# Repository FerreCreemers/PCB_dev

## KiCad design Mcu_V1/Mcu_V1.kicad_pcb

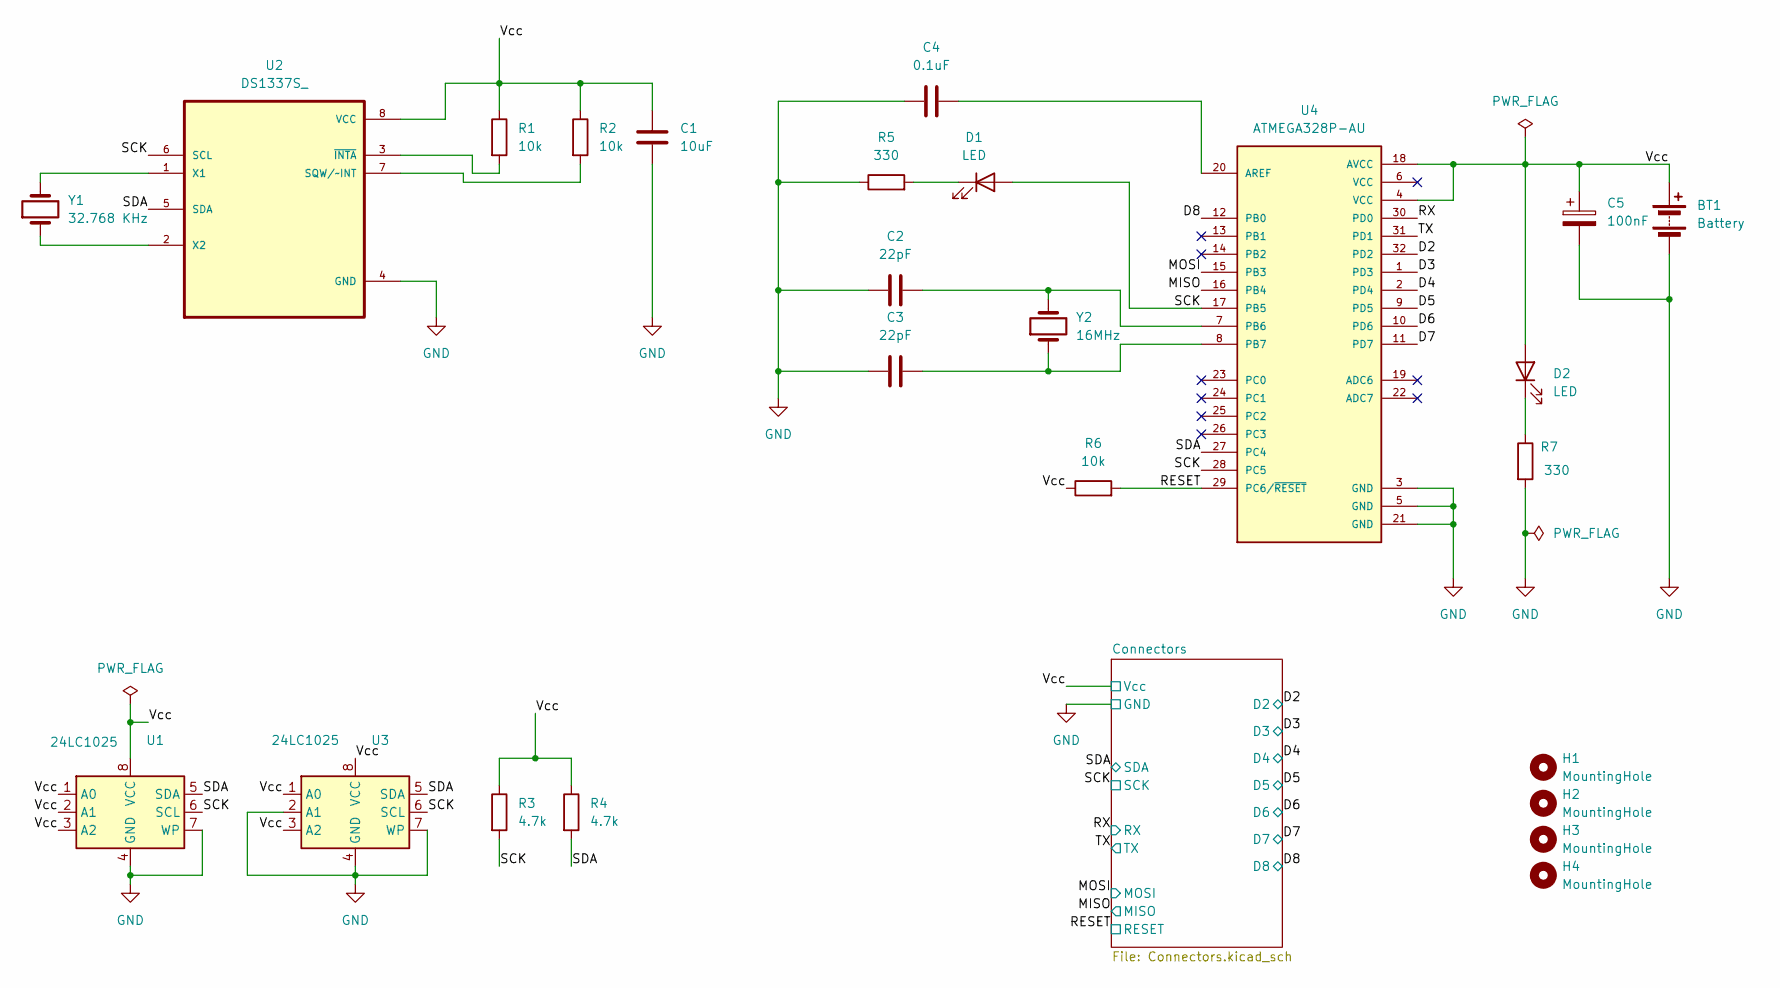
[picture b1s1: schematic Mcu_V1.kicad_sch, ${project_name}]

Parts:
BT1: Battery; PinHeader_1x02_P2.54mm_Vertical
C1: 10uF; C_0805_2012Metric
C2, C3: 22pF; C_0805_2012Metric
C4: 0.1uF; C_0805_2012Metric
C5: 100nF; C_0805_2012Metric
D1, D2: LED; LED_0805_2012Metric
H1, H2, H3, H4: MountingHole; MountingHole_2.1mm
R1, R2, R6: 10k; R_0805_2012Metric
R3, R4: 4.7k; R_0805_2012Metric
R5, R7: 330; R_0805_2012Metric
U1, U3: 24LC1025; SOIC-8_5.3x5.3mm_P1.27mm
U2: DS1337S_; SOIC127P600X175-8N
U4: ATMEGA328P-AU; QFP80P900X900X120-32N; PARTREV 8271A
Y1: 32.768 KHz; Crystal_SMD_5032-2Pin_5.0x3.2mm_HandSoldering
Y2: 16MHz; Crystal_SMD_5032-2Pin_5.0x3.2mm_HandSoldering

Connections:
/D2: U4.32 (PD2); also elsewhere on the board
/D3: U4.1 (PD3); also elsewhere on the board
/D4: U4.2 (PD4); also elsewhere on the board
/D5: U4.9 (PD5); also elsewhere on the board
/D6: U4.10 (PD6); also elsewhere on the board
/D7: U4.11 (PD7); also elsewhere on the board
/D8: U4.12 (PB0); also elsewhere on the board
/MISO: U4.16 (PB4); also elsewhere on the board
/MOSI: U4.15 (PB3); also elsewhere on the board
/RESET: R6.2, U4.29 (PC6/~RESET); also elsewhere on the board
/RX: U4.30 (PD0); also elsewhere on the board
/SCK: D1.2 (A), R3.2, U1.6 (SCL), U2.6 (SCL), U3.6 (SCL), U4.17 (PB5), U4.28 (PC5); also elsewhere on the board
/SDA: R4.2, U1.5 (SDA), U2.5 (SDA), U3.5 (SDA), U4.27 (PC4); also elsewhere on the board
/TX: U4.31 (PD1); also elsewhere on the board
GND: BT1.2 (-), C1.2, C2.1, C3.1, C4.1, C5.2, R5.1, R7.2, U1.4 (GND), U1.7 (WP), U2.4 (GND), U3.2 (A1), U3.4 (GND), U3.7 (WP), U4.3 (GND), U4.5 (GND), U4.21 (GND); also elsewhere on the board
unnamed: D1.1 (K), R5.2
unnamed: D2.1 (K), R7.1
unnamed: R2.2, U2.7 (SQW/~INT)
unnamed: U2.1 (X1), Y1.2
unnamed: U2.2 (X2), Y1.1
unnamed: R1.2, U2.3 (~INTA)
unnamed: C4.2, U4.20 (AREF)
unnamed: C2.2, U4.7 (PB6), Y2.2
unnamed: C3.2, U4.8 (PB7), Y2.1

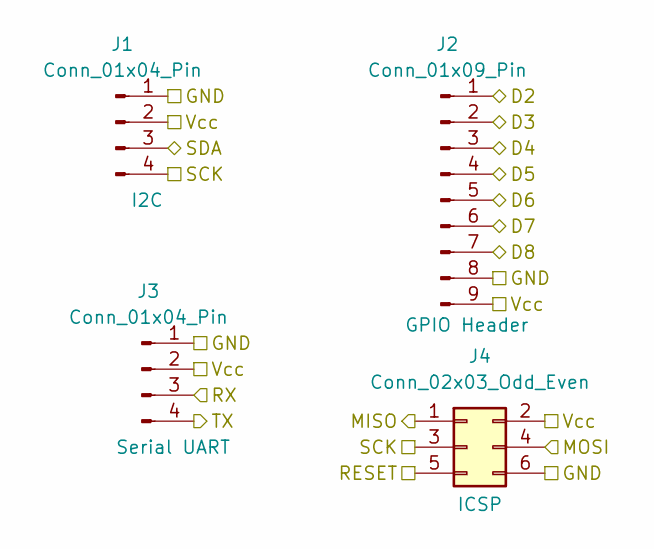
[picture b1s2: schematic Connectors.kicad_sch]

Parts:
J1, J3: Conn_01x04_Pin; PinHeader_1x04_P2.54mm_Vertical
J2: Conn_01x09_Pin; PinHeader_1x09_P2.54mm_Vertical
J4: Conn_02x03_Odd_Even; PinHeader_2x03_P2.54mm_Vertical

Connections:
/D2: J2.1; also elsewhere on the board
/D3: J2.2; also elsewhere on the board
/D4: J2.3; also elsewhere on the board
/D5: J2.4; also elsewhere on the board
/D6: J2.5; also elsewhere on the board
/D7: J2.6; also elsewhere on the board
/D8: J2.7; also elsewhere on the board
/MISO: J4.1; also elsewhere on the board
/MOSI: J4.4; also elsewhere on the board
/RESET: J4.5; also elsewhere on the board
/RX: J3.3; also elsewhere on the board
/SCK: J1.4, J4.3; also elsewhere on the board
/SDA: J1.3; also elsewhere on the board
/TX: J3.4; also elsewhere on the board
GND: J1.1, J2.8, J3.1, J4.6; also elsewhere on the board

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
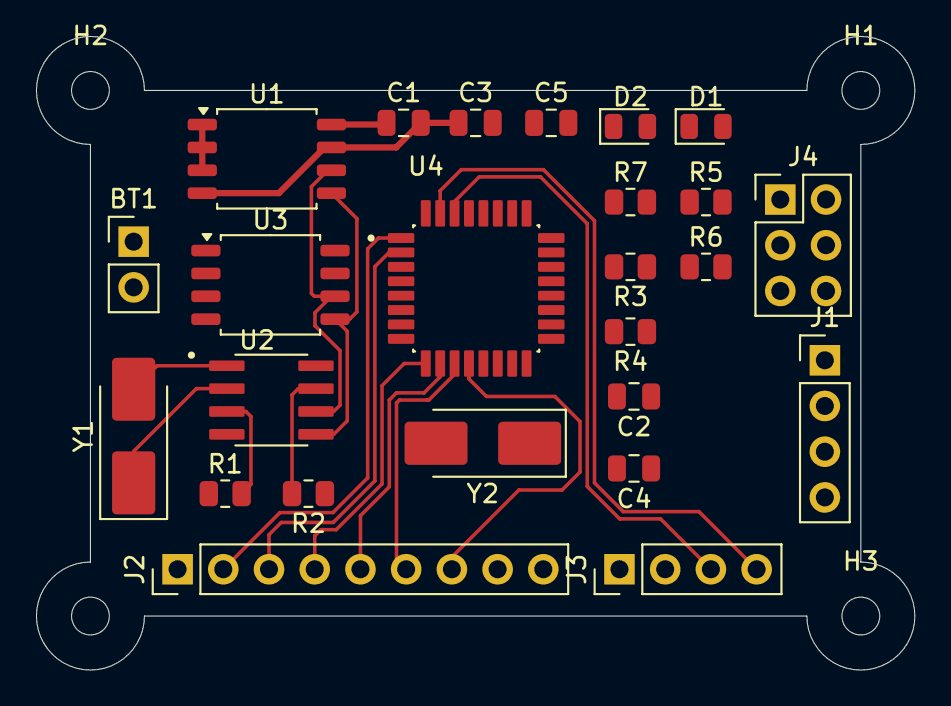
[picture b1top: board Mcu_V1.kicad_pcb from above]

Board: 4 copper layers, 48.8 x 35.2 mm, 29 parts (0 on the bottom side), 26 nets.

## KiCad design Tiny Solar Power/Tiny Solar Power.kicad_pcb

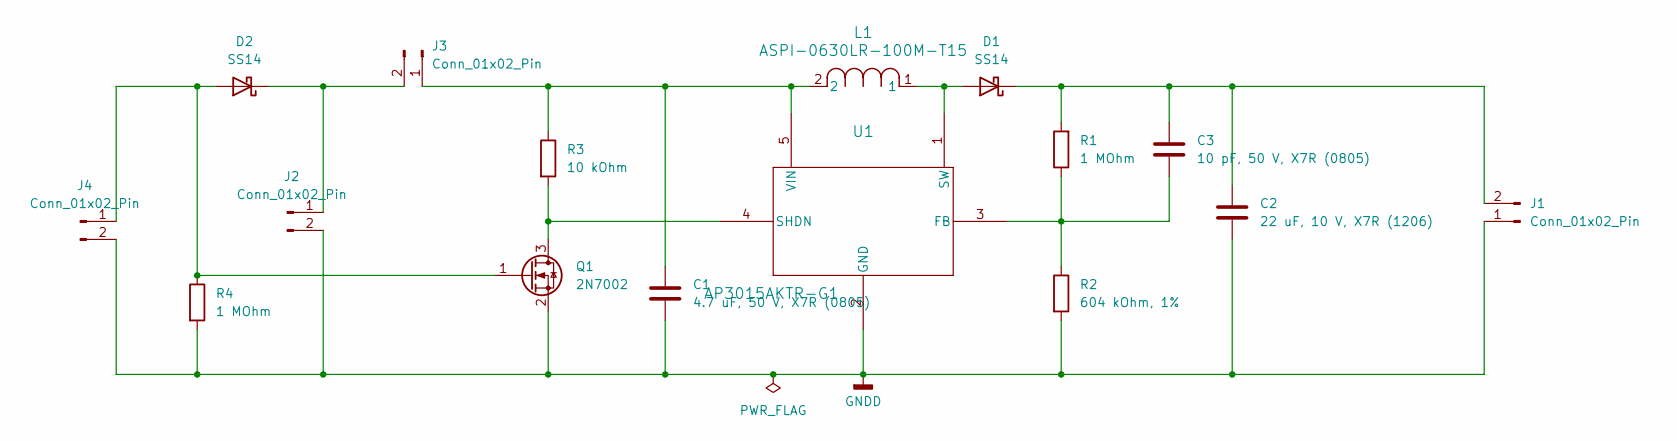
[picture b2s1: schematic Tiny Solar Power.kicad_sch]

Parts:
C1: 4.7 uF, 50 V, X7R (0805); C_0805_2012Metric
C2: 22 uF, 10 V, X7R (1206); C_1206_3216Metric
C3: 10 pF, 50 V, X7R (0805); C_0805_2012Metric
D1, D2: SS14; D_SMA
J1, J2, J3: Conn_01x02_Pin; PinHeader_1x02_P2.54mm_Vertical
J4: Conn_01x02_Pin; PinHeader_1x02_P2.54mm_Horizontal
L1: ASPI-0630LR-100M-T15; IND_ASPI-0630LR_ABR
Q1: 2N7002; SOT-23
R1, R4: 1 MOhm; R_0805_2012Metric
R2: 604 kOhm, 1%; R_0805_2012Metric
R3: 10 kOhm; R_0805_2012Metric
U1: AP3015AKTR-G1; SOT23-5_1P55X2P9_DIO

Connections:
/BAT_P: D2.1 (K), J2.1, J3.2
/OUT_P: C2.1, C3.1, D1.1 (K), J1.2, R1.2
/SOLAR_P: D2.2 (A), J4.1, Q1.1 (G), R4.1
GNDD: C1.2, C2.2, J1.1, J2.2, J4.2, Q1.2 (S), R2.2, R4.2, U1.2 (GND)
unnamed: D1.2 (A), L1.1, U1.1 (SW)
unnamed: C1.1, J3.1, L1.2, R3.1, U1.5 (VIN)
unnamed: Q1.3 (D), R3.2, U1.4 (SHDN)
unnamed: C3.2, R1.1, R2.1, U1.3 (FB)

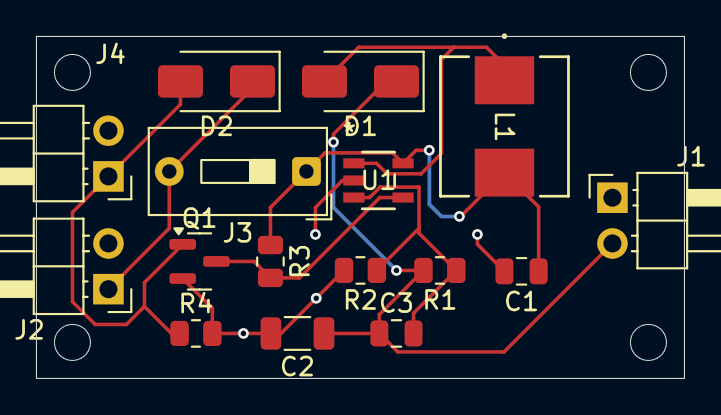
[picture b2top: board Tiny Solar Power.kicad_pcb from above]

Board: 2 copper layers, 36.0 x 19.0 mm, 16 parts (0 on the bottom side), 8 nets.

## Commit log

2025-08-08 small update
2025-08-08 symbols added
2025-08-08 annotation Symbols
2025-08-08 add com values
2025-08-11 update shematic
    completed wiring main sheet
2025-08-11 wiring done
2025-08-11 traces done
2025-08-12 4 layer done
